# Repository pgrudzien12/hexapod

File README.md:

<div align="center">

# Hexapod Locomotion Framework (ESP32)

| Supported Targets | ESP32 |
| ----------------- | ----- |

</div>

## 1. Project Overview
This repository contains firmware for a fully custom 6‑leg (hexapod) walking robot built around an ESP32 using the ESP‑IDF framework. The code implements a modular locomotion stack: user command capture → gait phase scheduling → swing trajectory generation → whole body inverse kinematics → servo actuation. All mechanical parts are custom designed and 3D printed.

Facts:
- Architecture design inspired by [Efficient gait generation and evaluation for hexapod robots (2024)](https://cjme.springeropen.com/articles/10.1186/s10033-024-01000-0)
- I burned three ESP32 dev boards during development and counting
- Project eaten up 2 months of my life up to the first release and working stage

## 2. Hardware Summary
* MCU / Control: ESP32 module (classic dual‑core variant) running FreeRTOS via ESP‑IDF
* Servos: 18 × high‑torque 35 kg.cm hobby servos (3 DOF per leg: coxa yaw, femur pitch, tibia)
* Power Architecture:
  * Main source: 4S LiPo battery
  * Each pair of legs (i.e. 6 servos) is powered by its own dedicated 20A UBEC (3 UBECs total for locomotion load distribution)
  * Logic / ESP32 / auxiliary electronics powered by a separate UBEC for isolation and brown‑out resilience
* Signal Driving:
  * Mixed use of MCPWM and LEDC peripherals to reach 18 PWM outputs on classic ESP32
  * Dynamic allocation strategy reuses MCPWM operators/generators and assigns some legs to LEDC channels
* Mechanical Structure: All joints, brackets, and chassis components are custom 3D printed (CAD‑designed) around standardized servo sizes and link lengths.

## 3. Mechanical & Kinematic Model
Each leg provides 3 degrees of freedom:
1. Coxa (yaw / horizontal rotation, establishing lateral reach)
2. Femur (pitch / vertical-plane lift)
3. Tibia (distal pitch / extension)

Nominal link lengths (meters) from `robot_config.c`:
* Coxa: 0.068 m
* Femur: 0.088 m
* Tibia: 0.127 m

Coordinate Frames:
* Body frame: X forward (+), Y left (+), Z up (+)
* Leg-local frame: X outward (+), Y forward (+), Z up (+) for planning; internally the IK expects Z downward in some comments but is reconciled via transforms in `whole_body_control.c`.

Mount poses (per leg) define (x, y, z, yaw) to rotate body-frame targets into leg-local coordinates. Yaw is ±90° plus minor angular offsets to create a symmetric stance.

## 4. Software Architecture
High-level data flow (single control task loop at 100 Hz / 10 ms):

1. `user_command_poll()` (in `user_command.c`)
	* Reads latest decoded RC controller state (`controller.c`) over FlySky iBUS via UART.
	* Produces normalized user command structure (`user_command_t`). Includes gait selection, enable flag, velocity command, body height, lateral offset, terrain mode, step scaling.
2. `gait_scheduler_update()` (in `gait_scheduler.c`)
	* Maintains a continuous phase 0..1 and per‑leg support vs swing state based on selected gait (Tripod, Ripple, Wave) and commanded speed.
3. `swing_trajectory_generate()` (in `swing_trajectory.c`)
	* Converts gait phase + user motion/pose targets into desired foot positions in the body frame.
	* Uses cycloid‑like arcs for swing, linear pass for support, adjustable step length and clearance.
4. `whole_body_control_compute()` (in `whole_body_control.c`)
	* Transforms each foot target from body frame into its corresponding leg-local frame using mount pose and yaw.
	* Solves per‑leg inverse kinematics (`leg_ik_solve()` from `leg.c`) to produce joint angles.
5. `robot_execute()` (in `robot_control.c`)
	* Maps joint angles (radians) into microsecond PWM pulses with calibration (limits, inversion, offsets) from `robot_config.c`.
	* Lazily initializes MCPWM / LEDC channels and updates compare or duty registers.

Supporting Modules:
* `robot_config.*` centralizes all geometry, calibration, servo driver selection, GPIO mappings, and stance parameters.
* `controller.*` encapsulates UART reception + decoding of iBUS frames with failsafe and deadband filtering.
* `leg.*` provides pure kinematic modeling (opaque handle + IK solver) decoupled from hardware.

### Main Loop (`main.c`)
The `gait_framework_main()` task sets a fixed timestep `dt=0.01f`, gathers user input, advances scheduler, generates trajectories, computes IK, and finally commands servos. Timing uses `esp_timer_get_time()` plus `vTaskDelay()` to maintain cadence while yielding to other tasks.

### Concurrency & Timing
* Currently a single high-level control loop task drives all locomotion logic.
* Controller UART reception runs in its own FreeRTOS task created by `controller_init()`; shared channel data is protected by a mutex.
* Future expansion could move heavy IK or trajectory computation to a dedicated high-priority task if needed.

## 5. Gait System
Implemented gait types (selectable via RC switch):
* Tripod (`GAIT_TRIPOD`): Alternating two groups of three legs. Provides fastest, most stable dynamic movement baseline.
* Ripple (`GAIT_RIPPLE`): Two legs swing at a time in three staggered windows (pairs determined by index % 3). Smoother COG shift.
* Wave (`GAIT_WAVE`): Single-leg swing progression for maximum static stability at lower speed.

Inspiration / References:
* Elements of phase grouping, stability considerations, and prospective optimization directions are informed by the research article: Efficient gait generation and evaluation for hexapod robots (2024) – https://cjme.springeropen.com/articles/10.1186/s10033-024-01000-0. The current implementation is a simplified, real‑time friendly subset and will evolve toward more quantitative energy/stability metrics.

Scheduler Logic:
* Maintains a normalized phase; frequency scaled by commanded forward velocity magnitude and a user step scaling knob.
* Determines each leg’s support/swing state, which the trajectory generator uses to choose stance vs swing profile.

Trajectory Highlights:
* Step length modulated by speed magnitude × user step_scale.
* Clearance height boosted when `terrain_climb` is active.
* Lateral body shift and vertical body height mapped from normalized inputs to meter ranges (configurable constants inside `swing_trajectory_init`).
* Uses proportion S of the phase cycle for swing (0<S<1) depending on gait (Tripod=0.5, Ripple≈0.33, Wave≈0.1).

## 6. Servo Control Strategy (18 PWM on ESP32)
Classic ESP32 has limited MCPWM operator capacity. This design:
* Reuses MCPWM timers/operators across channels (group pooling) to produce up to 12 channels.
* Assigns remaining joints to LEDC (50 Hz, 15-bit resolution) achieving additional PWM outputs.
* Calibration struct `joint_calib_t` defines per-joint direction (`invert_sign`), angle limits, and PWM µs mapping (default 500–2500 µs range, neutral 1500 µs).
* Lazy initialization ensures only needed peripherals are configured.

## 7. Development Environment
* IDE: Visual Studio Code with the official ESP‑IDF extension / environment.
* Build System: CMake generated by ESP‑IDF; project root contains `CMakeLists.txt` and `main/CMakeLists.txt`.
* Typical workflow:
  1. Configure target and flash settings in ESP‑IDF extension.
  2. Build (`idf.py build`) and flash (`idf.py flash`).
  3. Monitor logs (`idf.py monitor`) for control loop timing, servo init, and controller connection messages.

## 8. Visualization & Simulation
Complementary project for iterating on gait algorithms without hardware:
https://github.com/pgrudzien12/hexapod-visualizer

This external visualizer helps refine trajectory shapes, gait transitions, and future whole‑body control strategies before deployment on the physical robot.

## 9. Power & Safety Considerations
* Separate UBEC for logic prevents voltage sag from high servo load causing MCU resets.
* Distributing leg pairs across independent 20A UBECs reduces peak current concentration and wiring heating.
* RC arm/disarm switch (`enable` flag) prevents unintended motion during setup; when disabled, scheduler freezes and all legs remain in support state.
* Future: add soft-start ramp and watchdog to detect IK failures / out-of-reach foot targets.

## 10. Planned / Future Work
Short-term:
* Refine inverse kinematics limits and add reachability checks with graceful fallback per leg.
* Parameterize trajectory scaling (y range, height limits) via runtime configuration.

Mid-term:
* Modular controller input abstraction (initial implementation complete: FlySky iBUS driver + pluggable architecture for WiFi / BT).
* Web-based configuration interface (inspired by Betaflight) for tuning: servo calibration, gait parameters, stance geometry, safety thresholds.
* Persistent storage (NVS) for robot configuration instead of static initialization.
* Enhanced turning support: integrate yaw rate (`wz`) into per-leg lateral/forward offsets.

Long-term / Stretch:
* Add NVIDIA Jetson companion computer with stereoscopic depth camera for vision, terrain classification, and autonomous navigation (high-level planner sends velocity/pose commands to ESP32 locomotion layer).
* Terrain-adaptive foot placement (reactive height and lateral adjustment based on sensed surface). 
* State estimation fusing IMU and leg odometry.
* Energy-efficient gait optimization layer (multi-objective: power consumption vs stability vs speed), extending ideas from the referenced 2024 hexapod gait research to adapt duty factor and phase offsets on-the-fly.

## 11. Repository Structure (Key Files)
* `main/main.c` – Control loop entry point.
* `main/gait_scheduler.*` – Phase management & leg support/swing pattern logic.
* `main/swing_trajectory.*` – Foot trajectory generation from scheduler + user command.
* `main/whole_body_control.*` – Frame transforms & IK orchestration.
* `main/robot_control.*` – Joint angle to PWM mapping, peripheral management (MCPWM + LEDC).
* `main/robot_config.*` – Central configuration: geometry, calibration, mounts, driver selection.
* `main/leg.*` – Pure kinematic leg model & IK solver.
* `main/controller.*` – RC receiver (iBUS) decoding & normalization.
* `main/controller_flysky_ibus.c` – FlySky iBUS driver (UART task) feeding abstraction.
* `main/controller_internal.h` – Internal helpers for controller drivers.
* `main/user_command.*` – Aggregates controller state into locomotion command.

## 12. Getting Started (Build & Flash)
1. Install ESP‑IDF (v5.x recommended) and export environment.
2. Connect ESP32 over USB.
3. (Optional) Edit GPIO mappings / driver selections in `robot_config.c` before first flash.
4. Build & flash.
5. Power servos from their UBECs only after confirming logic supply is stable.

## 13. Notes on Customization
* Adjust leg geometry: change lengths in `leg_config_t` initialization before calling `leg_configure()`.
* Tune servo mappings: update `joint_calib_t` ranges & neutral offsets in `robot_config_init_default()`.
* Add new gait: extend `gait_type_t`, expand switch in `gait_scheduler_update()` and adapt `swing_trajectory_generate()` for phase offset logic.

### Controller Abstraction & Future Runtime Swapping

The controller layer now provides a driver abstraction. Key points:

* Each driver spins a FreeRTOS task ingesting raw input (UART, TCP socket, Bluetooth) then updates a shared signed channel array (32 × int16_t, range -32768..32767) guarded by a mutex.
* Existing APIs `controller_get_channels()` and `controller_decode()` remain stable; locomotion stack is transport‑agnostic.
* Failsafe injects neutral (zero) channels when a driver times out or disconnects.
* Current driver: FlySky iBUS over UART (default) – its 1000..2000 values are rescaled into full signed range for first 14 slots; remaining slots zero.
* WiFi TCP driver (added): versioned binary frame (74 bytes) with sync (AA55), header, 32 signed channels, CRC16.
	* Detailed spec: see `WIFI_TCP_PROTOCOL.md`.
	* Current network mode: AP-only for simplicity (see `WIFI_NETWORK_MODES.md` for evolution plan to AP+STA).
	* AP SSID generation supports fixed, MAC-suffix, or random-suffix modes (default = MAC suffix, e.g. `HEXAPOD_AP_3AF2B7`).
* Opaque driver configuration: `controller_config_t` holds a `driver_cfg` pointer + size (e.g. `controller_flysky_ibus_cfg_t`). This keeps core lean while enabling WiFi / BT specific parameters. Memory ownership is with caller.
* Developer guide for writing new drivers: see `CONTROLLER_DRIVERS.md`.
* (Early draft WiFi packet format removed; see `WIFI_TCP_PROTOCOL.md` for the authoritative current definition.)

Runtime selection (future): store selected driver + params (e.g. WiFi port, BT service UUID) in NVS, applied at boot so firmware can remain static while changing control sources from the portal.

## 14. License
This project is licensed under the Apache License, Version 2.0. See the `LICENSE` file at the repository root for the full text.

Include the following notice in derivative works:

```
Copyright 2025 Paweł Grudzień

Licensed under the Apache License, Version 2.0 (the "License");
you may not use this file except in compliance with the License.
You may obtain a copy of the License at

	http://www.apache.org/licenses/LICENSE-2.0

Unless required by applicable law or agreed to in writing, software
distributed under the License is distributed on an "AS IS" BASIS,
WITHOUT WARRANTIES OR CONDITIONS OF ANY KIND, either express or implied.
See the License for the specific language governing permissions and
limitations under the License.
```

Some source files retain original ESP‑IDF Apache 2.0 headers; new modules follow the same license.

---
If you build upon this project, a link back or a star is appreciated. Contributions (PRs) for new gaits, better IK, or configuration UI are welcome.

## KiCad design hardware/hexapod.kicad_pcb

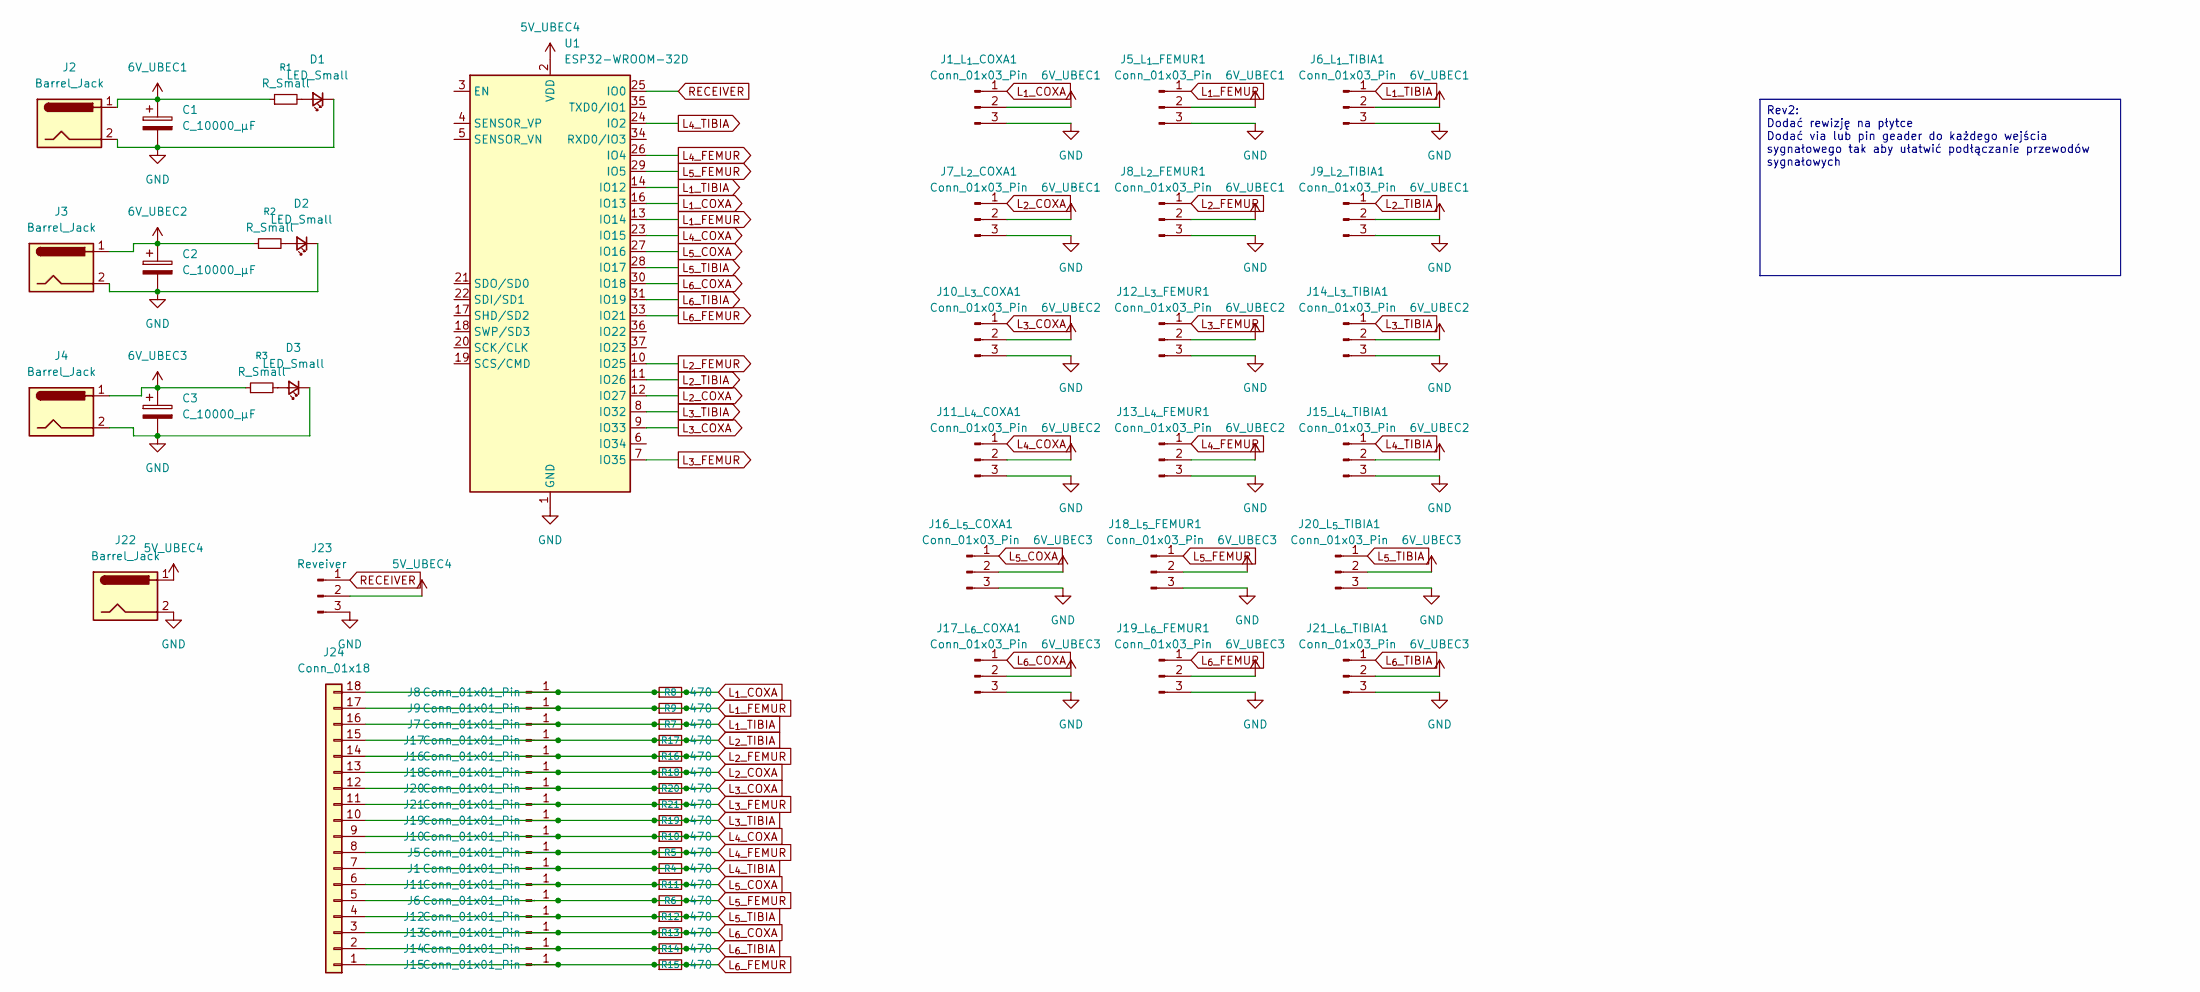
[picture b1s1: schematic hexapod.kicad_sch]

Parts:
C1, C2, C3: C_10000_µF; CP_Radial_D16.0mm_P7.50mm
D1, D2, D3: LED_Small; LED_0805_2012Metric
J1, J5, J6, J7, J8, J9, J10, J11, J12, J13, J14, J15, J16, J17, J18, J19, J20, J21: Conn_01x01_Pin; PinHeader_1x01_P2.54mm_Vertical
J1_L_{1}_COXA1, J5_L_{1}_FEMUR1, J6_L_{1}_TIBIA1, J10_L_{3}_COXA1, J11_L_{4}_COXA1, J12_L_{3}_FEMUR1, J13_L_{4}_FEMUR1, J14_L_{3}_TIBIA1, J15_L_{4}_TIBIA1, J17_L_{6}_COXA1, J19_L_{6}_FEMUR1, J21_L_{6}_TIBIA1: Conn_01x03_Pin; PinHeader_1x03_P2.54mm_Horizontal
J2, J3, J4, J22: Barrel_Jack; TerminalBlock_Phoenix_MKDS-1,5-2_1x02_P5.00mm_Horizontal
J7_L_{2}_COXA1, J8_L_{2}_FEMUR1, J9_L_{2}_TIBIA1, J16_L_{5}_COXA1, J18_L_{5}_FEMUR1, J20_L_{5}_TIBIA1: Conn_01x03_Pin; PinHeader_1x03_P2.54mm_Vertical
J23: Reveiver; PinHeader_1x03_P2.54mm_Vertical
J24: Conn_01x18; TE_1-84952-8_1x18-1MP_P1.0mm_Horizontal
R1, R2, R3: R_Small; R_0805_2012Metric
R4, R5, R6, R7, R8, R9, R10, R11, R12, R13, R14, R15, R16, R17, R18, R19, R20, R21: 470; R_0805_2012Metric_Pad1.20x1.40mm_HandSolder
U1: ESP32-WROOM-32D; ESP32_Dev_Board

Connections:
6V_UBEC1: C1.1, J1_L_{1}_COXA1.2, J2.1, J5_L_{1}_FEMUR1.2, J6_L_{1}_TIBIA1.2, J7_L_{2}_COXA1.2, J8_L_{2}_FEMUR1.2, J9_L_{2}_TIBIA1.2, R1.1
6V_UBEC2: C2.1, J3.1, J10_L_{3}_COXA1.2, J11_L_{4}_COXA1.2, J12_L_{3}_FEMUR1.2, J13_L_{4}_FEMUR1.2, J14_L_{3}_TIBIA1.2, J15_L_{4}_TIBIA1.2, R2.1
6V_UBEC3: C3.1, J4.1, J16_L_{5}_COXA1.2, J17_L_{6}_COXA1.2, J18_L_{5}_FEMUR1.2, J19_L_{6}_FEMUR1.2, J20_L_{5}_TIBIA1.2, J21_L_{6}_TIBIA1.2, R3.1
GND: C1.2, C2.2, C3.2, D1.1 (K), D2.1 (K), D3.1 (K), J1_L_{1}_COXA1.3, J2.2, J3.2, J4.2, J5_L_{1}_FEMUR1.3, J6_L_{1}_TIBIA1.3, J7_L_{2}_COXA1.3, J8_L_{2}_FEMUR1.3, J9_L_{2}_TIBIA1.3, J10_L_{3}_COXA1.3, J11_L_{4}_COXA1.3, J12_L_{3}_FEMUR1.3, J13_L_{4}_FEMUR1.3, J14_L_{3}_TIBIA1.3, J15_L_{4}_TIBIA1.3, J16_L_{5}_COXA1.3, J17_L_{6}_COXA1.3, J18_L_{5}_FEMUR1.3, J19_L_{6}_FEMUR1.3, J20_L_{5}_TIBIA1.3, J21_L_{6}_TIBIA1.3, J22.2, J23.3, U1.1 (GND), U1.15 (GND), U1.38 (GND), U1.39 (GND)
L_{1}_COXA: J1_L_{1}_COXA1.1, J8.1, J24.18, R8.1, R8.2, U1.16 (IO13)
L_{1}_FEMUR: J5_L_{1}_FEMUR1.1, J9.1, J24.17, R9.1, R9.2, U1.13 (IO14)
L_{1}_TIBIA: J6_L_{1}_TIBIA1.1, J7.1, J24.16, R7.1, R7.2, U1.14 (IO12)
L_{2}_COXA: J7_L_{2}_COXA1.1, J18.1, J24.13, R18.1, R18.2, U1.12 (IO27)
L_{2}_FEMUR: J8_L_{2}_FEMUR1.1, J16.1, J24.14, R16.1, R16.2, U1.10 (IO25)
L_{2}_TIBIA: J9_L_{2}_TIBIA1.1, J17.1, J24.15, R17.1, R17.2, U1.11 (IO26)
L_{3}_COXA: J10_L_{3}_COXA1.1, J20.1, J24.12, R20.1, R20.2, U1.9 (IO33)
L_{3}_FEMUR: J12_L_{3}_FEMUR1.1, J21.1, J24.11, R21.1, R21.2, U1.7 (IO35)
L_{3}_TIBIA: J14_L_{3}_TIBIA1.1, J19.1, J24.10, R19.1, R19.2, U1.8 (IO32)
L_{4}_COXA: J10.1, J11_L_{4}_COXA1.1, J24.9, R10.1, R10.2, U1.23 (IO15)
L_{4}_FEMUR: J5.1, J13_L_{4}_FEMUR1.1, J24.8, R5.1, R5.2, U1.26 (IO4)
L_{4}_TIBIA: J1.1, J15_L_{4}_TIBIA1.1, J24.7, R4.1, R4.2, U1.24 (IO2)
L_{5}_COXA: J11.1, J16_L_{5}_COXA1.1, J24.6, R11.1, R11.2, U1.27 (IO16)
L_{5}_FEMUR: J6.1, J18_L_{5}_FEMUR1.1, J24.5, R6.1, R6.2, U1.29 (IO5)
L_{5}_TIBIA: J12.1, J20_L_{5}_TIBIA1.1, J24.4, R12.1, R12.2, U1.28 (IO17)
L_{6}_COXA: J13.1, J17_L_{6}_COXA1.1, J24.3, R13.1, R13.2, U1.30 (IO18)
L_{6}_FEMUR: J15.1, J19_L_{6}_FEMUR1.1, J24.1, R15.1, R15.2, U1.33 (IO21)
L_{6}_TIBIA: J14.1, J21_L_{6}_TIBIA1.1, J24.2, R14.1, R14.2, U1.31 (IO19)
unnamed: D1.2 (A), R1.2
unnamed: D2.2 (A), R2.2
unnamed: D3.2 (A), R3.2
unnamed: J22.1, J23.2, U1.2 (VDD)
unnamed: J23.1, U1.25 (IO0)

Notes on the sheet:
Rev2: Dodać rewizję na płytce Dodać via lub pin geader do każdego wejścia sygnałowego tak aby ułatwić podłączanie przewodów sygnałowych

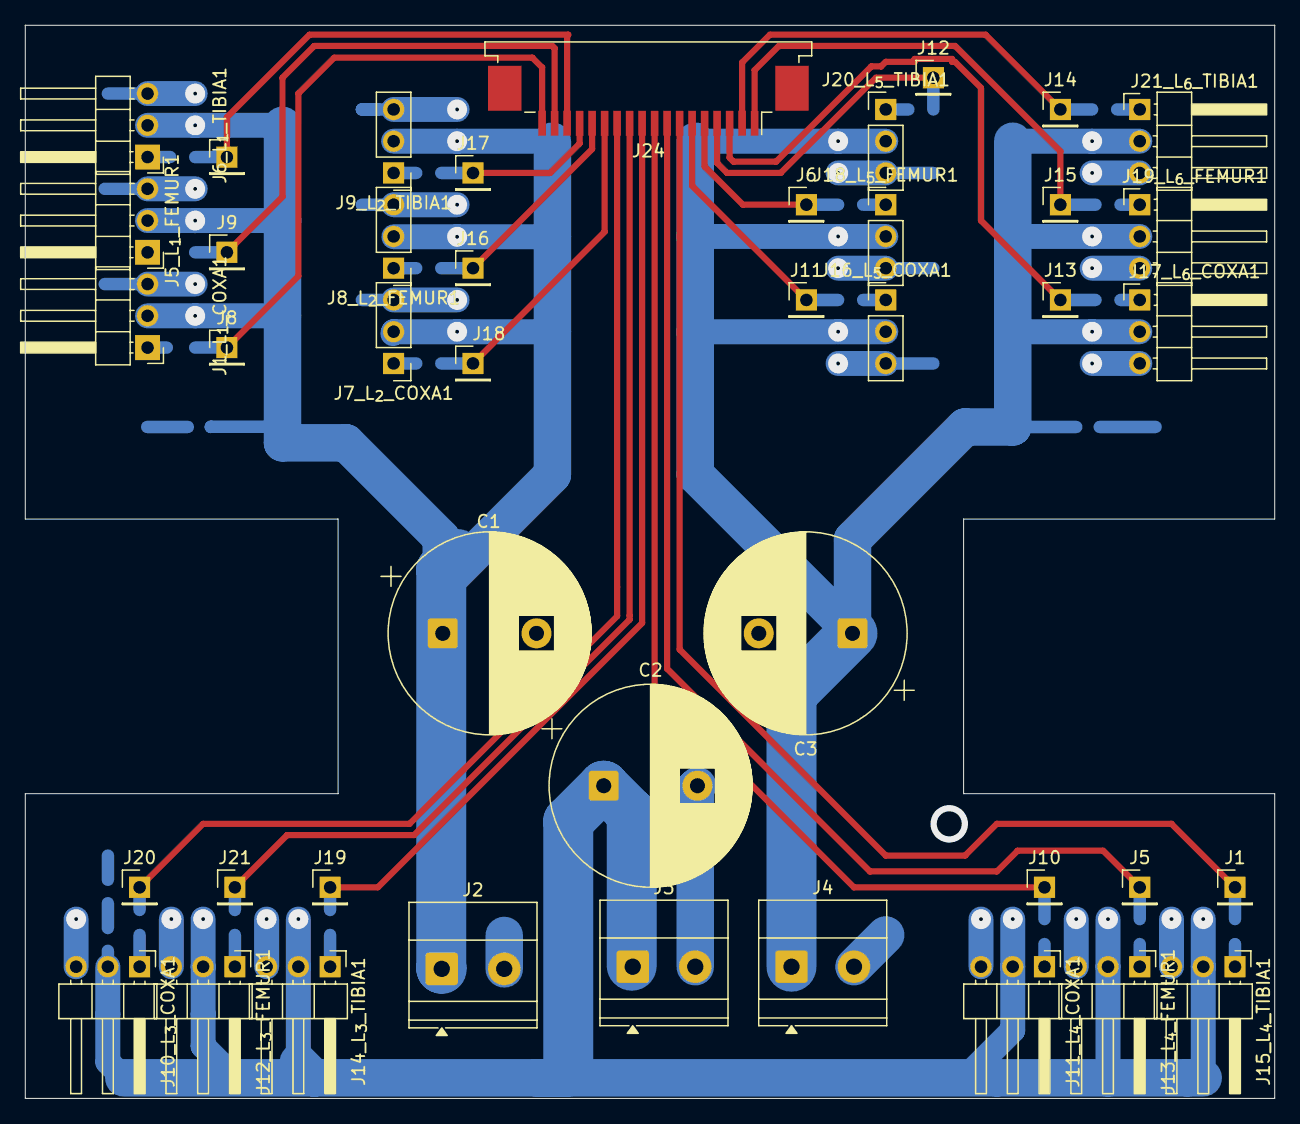
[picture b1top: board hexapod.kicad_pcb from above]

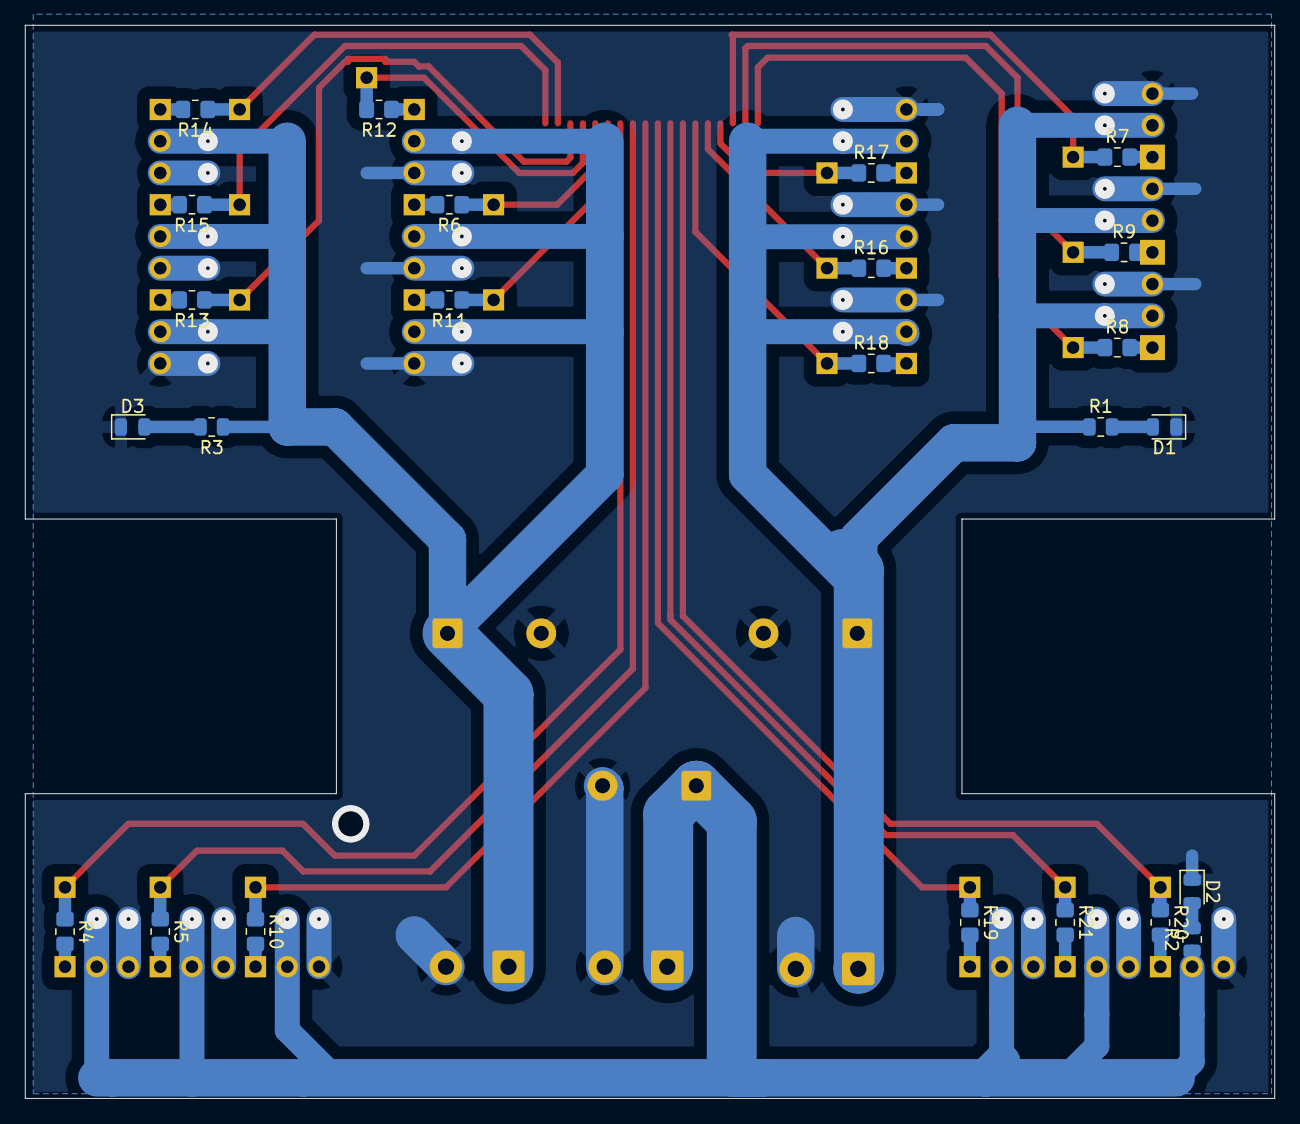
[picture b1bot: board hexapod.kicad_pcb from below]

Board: 2 copper layers, 99.9 x 85.9 mm, 67 parts (24 on the bottom side), 25 nets.

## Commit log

2025-08-22 initial code
2025-08-22 leg descriptor
2025-08-24 IK for a leg
2025-08-24 softcode offsets
2025-08-25 fixed IK
2025-08-30 change logging to debug
2025-08-30 initial implementation of the framework
2025-08-30 cycloid trajectory
2025-08-30 doc update
2025-08-30 deadband and scaling
2025-08-30 asserts
2025-08-30 redesign ripple to user two legs
2025-08-30 min/max z
2025-08-30 change default max z
2025-08-31 config and initial impl of body control
2025-08-31 before build fixes; more confgig
2025-08-31 build fix
2025-08-31 fixed config and more logging
2025-08-31 controller default gpio set
2025-08-31 leg debugger
2025-08-31 fix leg movement up/down when no velocity
2025-08-31 wbc fixed
2025-08-31 sholud be working
2025-09-18 working legs, I think
2025-09-18 working legs, I think 2
2025-09-19 small refactoring
2025-09-21 rm leg debugger
2025-09-21 distribute lines in config
2025-09-21 fix legs groups
2025-09-21 consistent loops wait
2025-09-21 little cleanup
2025-09-23 more changes but I beleve I mixed coordiate systems LHS - global and RHS in legs
2025-09-25 moved to rhs coordinate systems with z up
2025-10-07 add selection of pwm driver; tuning and config
2025-10-07 docs and license
2025-10-07 docs and license fix
2025-10-07 comment out zero angle test
2025-10-07 add info to readme
2025-10-11 fix license, add debug for controller
2025-10-11 abstract driver from controller to allow for wifi controller implementation
2025-10-11 making controller use int values
2025-10-11 inital wifi implementation
2025-10-11 fix wifi tcp
2025-10-11 more wifi impl
2025-10-11 bt contorller
2025-10-11 start with ct controller
2025-10-11 working bt controller
2025-10-12 GPIO assignments
2025-10-12 turning
2025-10-12 reset when no movement
2025-10-19 configuration on fat filesystem
2025-10-19 sdkconfig
2025-10-19 fix problems and add sdkconfig
2025-10-19 no BLE
2025-10-22 forward kinematics and pose estimation; not tested!
2025-10-25 kpp before testing
2025-10-25 small cleanup
2025-10-26 fix build/bt connection, shut down kpp_updaste_state as its buggy or not tuned properly
2025-10-26 kpp redesigned
2025-10-26 debug kpp
2025-11-02 new todo
2025-11-02 add configurator page TOOD:
2025-11-06 persistance layer design
2025-11-06 feat: Add NVS-based configuration persistence system with dual partitions and live parameter tuning
2025-11-06 Refactor config persistence with clean migration architecture and global version management
2025-11-06 reduce log noise
2025-11-08 change approach to configuration
2025-11-09 simplify config and bring back uint type
2025-11-09 rpc system design
2025-11-09 simplify rpc plan
2025-11-10 rpc using bluetooth
2025-11-10 abstraction for rpc layer plus wortking wifi
2025-11-17 working wifi rpc
2025-11-17 redesign controller communication
2025-11-17 remove debug logs
2025-11-18 improve flysky
2025-11-19 wifi always enabled
2025-11-22 joint_cal namespace and rpc
2025-11-23 remove descriptions; add refactor plan
2025-11-30 refactoring plan
2025-11-30 refactoring plan rev 2
2026-01-22 initail components structure
2026-01-22 new components
2026-02-02 partial refactoring to components
2026-02-03 kicad board prototype
2026-02-04 add FFC connector
